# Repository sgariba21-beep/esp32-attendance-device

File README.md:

# ESP32 Fingerprint Attendance System

Ghanaian schools and institutions still take attendance on paper. A teacher calls a register, marks each name by hand, then copies the totals into another book or a spreadsheet. Roll-call takes class time and the handwritten tallies are easy to miscount and slow to total across a term. This system replaces the register with a fingerprint scan.

An ESP32 device with an R503 fingerprint sensor records each scan, and a Next.js dashboard backed by Supabase handles reporting and the day-to-day management of devices and members. One cloud Supabase project serves every institution, with each tenant's data isolated from the rest. It is in use at two schools and an office, with 13 devices and about 400 active members between them (see [Real-World Deployment](#real-world-deployment)).

---

## Why This Exists

- Ghanaian schools and small institutions track attendance on paper or not at all; the affordable end of the market has no biometric option tied to a reporting dashboard.
- ZKTeco and similar incumbents ship standalone terminals with no multi-tenant cloud dashboard and no remote device management.
- The system is built around term and academic-year structure, with institution type configurable as school, office, or shop.
- Each device is built from off-the-shelf parts at about GHS 1,000.
- The firmware and dashboard are AGPL-3.0 on GitHub; institutions can self-host or use the managed hosted service.

---

## Real-World Deployment

The system is in use at three sites: two schools and an office.

| Deployment | Sites | Devices | Active members |
|---|---|---|---|
| This repo (hosted service) | 1 school, 1 office | 2 | ~100 |
| OLAG (private repo) | 1 school | 11 | ~300 |
| **Total** | **3** | **13** | **~400** |

- **This repo.** One school and one office run on the hosted multi-tenant service, with one device each.
- **OLAG.** The second school has 11 devices: 10 for classes and 1 for its robotics club, which runs in club (meeting-based) mode. OLAG runs the same attendance system, with the same firmware, dashboard, and backend design. It lives in a separate repository with its own Supabase project and Vercel deployment because the school wanted private ownership of its source code.

---

## Architecture

```
┌─────────────────────────────┐
│       ESP32 Devices         │
│  R503 fingerprint sensor    │
│  One device per unit        │
└────────────┬────────────────┘
             │ HTTPS (x-device-secret / x-bootstrap-secret)
             ▼
┌─────────────────────────────┐
│  Supabase Edge Functions    │
│  (cloud)                    │
│  log-attendance             │
│  mark-absent (pg_cron)      │
│  get-enrollment-job         │
│  update-enrollment-job      │
│  register                   │
│  assignment-poll            │
└────────────┬────────────────┘
             │ service role
             ▼
┌─────────────────────────────┐
│   Supabase PostgreSQL       │
│   (cloud)                   │
│   Multi-tenant schema       │
│   RLS policies (defence-in- │
│   depth; dormant for svc    │
│   role access)              │
└─────────────────────────────┘
             ▲
             │ server-side only (service role)
┌────────────┴────────────────┐
│     Next.js Dashboard       │
│     Deployed on Vercel      │
│  All Supabase calls are     │
│  server-side (no browser    │
│  exposure of keys)          │
└─────────────────────────────┘
```

---

## Tech Stack

| Layer | Technology |
|---|---|
| Firmware | Arduino (ESP32), FreeRTOS, R503 fingerprint library, SH1106 OLED (Adafruit SH110X + GFX) |
| Database | Supabase (cloud PostgreSQL + Auth + Storage + pg_cron) |
| Edge functions | Deno (Supabase Edge Functions) |
| Dashboard | Next.js App Router, shadcn/ui, TailwindCSS |
| Dashboard PWA | Installable web app — `manifest.webmanifest` + a minimal service worker (installability only, no offline cache) and an in-app install prompt |
| Hosting | Vercel (dashboard) |

> **Note on Next.js:** This project uses a version with breaking API changes from standard Next.js. Middleware lives in `frontend/proxy.ts`, not `middleware.ts`. Read `frontend/AGENTS.md` before writing any Next.js code.

---

## Hardware

### Components

| Component | Spec |
|---|---|
| Microcontroller | ESP32 (dual-core, 240 MHz) |
| Fingerprint Sensor | R503 Capacitive |
| RTC Module | DS3231 |
| Display (optional) | SH1106 1.3" 128×64 I²C OLED @ address 0x3C (a 0.96" SSD1306 needs the pre-1.12.0 driver) — the firmware runs headless if it is absent or fails to init |
| Carrier PCB | Custom 2-layer KiCad interconnect board — no active parts; seats the ESP32 module and provides keyed connectors for the R503 (JST-SH), the RTC + OLED I²C group, and a JST-GH 5 V input. Source in [`hardware/PCBs/`](hardware/PCBs/) |
| Enclosure | 3D-printed base + lid (+ an OLED bezel variant for display builds). FreeCAD source and print-ready 3MF in [`hardware/CAD files/`](hardware/CAD%20files/) |
| Fasteners | M3 screws + M3 heat-set inserts — the brass inserts are melted into the printed enclosure with a soldering iron, and the screws thread into them |

### Wiring

| Signal | ESP32 Pin |
|---|---|
| R503 TX → ESP32 RX | GPIO 16 |
| R503 RX → ESP32 TX | GPIO 17 |
| DS3231 SDA | GPIO 21 |
| DS3231 SCL | GPIO 22 |
| OLED SDA | GPIO 21 (shared I²C bus with the DS3231) |
| OLED SCL | GPIO 22 (shared I²C bus with the DS3231) |

---

## Firmware Architecture

Single sketch: `firmware/ClassAttendance_Current_RTC/ClassAttendance_Current_RTC.ino`. Three FreeRTOS tasks pinned across the two cores.

### Tasks

| Task | Core | Responsibility |
|---|---|---|
| `FingerprintTask` | 1 | Scan loop, match against the local fid map, LED feedback, enrollment execution, captive-portal launch on master-finger scan. Writes each scan to SPIFFS then signals `NetworkTask` via binary semaphore. |
| `NetworkTask` | 0 | Provisioning, waiting on scan semaphore from `FingerprintTask`, rotate-then-process SPIFFS queue flush to `log-attendance`, NTP→RTC sync, WiFi reconnect, and a server-reachability watchdog that reboots the device after a sustained inability to reach the backend. |
| `EnrollmentTask` | 0 | Polls `get-enrollment-job`, hands jobs to `FingerprintTask`, reports results durably (retried until acknowledged), acts on the decommission signal (wipes identity and reboots into provisioning). |

Inter-task communication:

- `memQueueSem` is a binary semaphore used only as a signal: `FingerprintTask` gives it after writing a scan to SPIFFS; `NetworkTask` waits on it (or a 15 s periodic timeout) before calling `flushQueue()`. There is no in-memory scan queue.
- Enrollment jobs pass from `EnrollmentTask` to `FingerprintTask` through `currentEnrollJob`, guarded by `enrollMutex` and signalled by `enrollSem`.
- `spiffsMutex` serialises every SPIFFS access across all three tasks.

### Display (OLED)

An optional 1.3" SH1106 128×64 panel on the shared I²C bus. `display.begin()` is attempted once in `setup()`; on failure `displayAvailable = false` and the firmware runs headless with no behaviour change. There is no dedicated display task — rendering is driven from a Core-0-safe mailbox. Tasks post card state (idle clock, scan verdict, enrollment step, master-finger confirm, provisioning, OTA) into the mailbox and never touch the `display` object directly. Tier-2 status (queue depth, dropped-record count, degraded / offline) is overlaid on the idle screen; the panel sleeps after 120 s idle and wakes on the next event. The per-institution `member_name_display` setting (fetched via `get-enrollment-job`, cached in SPIFFS with `config_rev`) controls how much of a member's name a scan card shows.

### Offline queue

- **Durability-first:** each scan is written to `/queue.txt` in SPIFFS synchronously inside `FingerprintTask` before any network attempt. The scan is never held only in RAM.
- **Rotate-then-process:** when `NetworkTask` flushes, it atomically renames `/queue.txt` → `/queue_inflight.txt` under the lock, then releases the lock. `FingerprintTask` can keep appending to a fresh `/queue.txt` while the network send runs without holding `spiffsMutex`.
- **Crash recovery:** if power is cut mid-flush, `/queue_inflight.txt` is orphaned. On the next boot, `recoverInflightQueue()` runs before tasks start and merges it back into `/queue.txt`.
- On flush, 5xx/429/network errors keep a record for retry; 4xx drops it.
- Caps: 1000 entries, 256 KB, 7-day age. Oldest records are trimmed first.

### Scan IDs

Each scan gets a `scan_id` of `scan-YYYYMMDDhhmmss-<member-sid>`, with the timestamp read from the DS3231 RTC. The RTC clock survives reboots and power loss and is synced from NTP on boot and after each reconnect.

### OTA

- On boot, with WiFi up and assignment not pending, the device waits a random jitter of 0–120 s (seeded from hardware entropy) before checking for updates. This prevents a fleet-wide power blip from hitting GitHub's 60 req/hr unauthenticated rate limit simultaneously.
- The device GETs `releases/latest` from the GitHub API. Release tags must be `firmware-v<major>.<minor>.<patch>`. The tag version is compared against the compiled-in `FIRMWARE_VERSION`; only a strictly newer version flashes.
- The release's `.bin` asset is streamed through the `Update` library. The sensor LED holds red while writing, and the device reboots into the new image on success.

---

## Database Schema

All dashboard data access uses `createAdminClient()` (service role — bypasses RLS). RLS policies exist as defence-in-depth and will become load-bearing if authenticated client access is introduced.

```sql
-- Institution registry (one row per tenant)
-- type: 'school' | 'office' | 'shop'
-- theme_primary: hex brand colour injected as CSS custom properties server-side (no FOUC)
-- theme_preset: curated palette key (e.g. 'indigo', 'rose') or 'custom'; null → platform default
-- device_secret: shared bootstrap secret — TRANSITIONAL. Will be removed once all
--   devices have been re-provisioned with per-device secrets (devices.device_secret).
-- tracked_weekdays: smallint[] of ISO weekday numbers (1=Mon … 7=Sun) attendance is
--   tracked on. Replaces the removed skip_weekends boolean. log-attendance ignores
--   scans on other days; mark-absent generates no rows for them.
-- time_format: '12h' | '24h' — dashboard clock rendering only; stored times stay UTC / 24h.
-- track_lateness / expected_start_time / late_grace_minutes and
--   track_early_leaving / expected_end_time / early_leave_grace_minutes:
--   optional per-institution punctuality thresholds that drive attendance.punctuality.
-- member_name_display: 'full' | 'first' | 'initial_last' | 'sid' | 'none' — how much of a
--   member's name the device OLED shows on a scan card (enrollment always shows the full name).
-- currency: ISO-4217 display currency for the retail module (formatting only, no FX).
-- sell_products / sell_services / loyalty_enabled: shop-module switches.
-- status: 'active' | 'suspended' | 'deactivated' — non-active tenants are gated to /suspended.
-- config_rev: bigint bumped by the institutions_touch trigger on any row change; the device
--   polls it to know its cached device_config is stale. updated_at is bumped by the same trigger.
institutions    (id, name, type, logo_url, label_member, label_members, label_group,
                 label_unit, label_period, label_staff, label_staff_plural,
                 track_students, track_staff, student_scan_mode, staff_scan_mode,
                 tracked_weekdays, timezone, time_format, track_lateness,
                 expected_start_time, late_grace_minutes, track_early_leaving,
                 expected_end_time, early_leave_grace_minutes, member_name_display,
                 currency, sell_products, sell_services, loyalty_enabled, status,
                 device_secret, config_rev, created_at, updated_at,
                 theme_primary, theme_preset)

-- Members (students, staff, customers, etc.) — scoped to institution
-- member_type: 'student' | 'staff'  (default 'student')
-- sid is UNIQUE PER INSTITUTION (institution_id, sid), not globally
-- device_id FK is ON DELETE SET NULL (device deletion preserves member records)
members         (id, sid, fullname, group_name, unit_name, fin1, fin2, status, member_type,
                 device_id→devices SET NULL, institution_id, created_at)

-- One ESP32 per unit — scoped to institution
-- device_secret: per-device secret issued at provisioning time by /assignment-poll
-- revoked: true blocks the device from logging attendance (instant lockout)
-- provisioning_token: issued by /register, required by /assignment-poll (H7)
devices         (id, group_name, unit_name, display_name, mac, provisioning_token,
                 device_secret, revoked, institution_id)

-- Academic periods — scoped to institution (nullable for office/shop-type institutions)
periods         (id, term, year, status, start_date, end_date, institution_id)

-- Attendance records — scoped to institution
-- status: 'present' | 'absent'
-- scan_type: 'present' | 'time_in' | 'time_out'  (CHECK constraint — 'absent' is a status, not a scan_type)
-- punctuality: 'on_time' | 'late' | 'early_leave' | null — verdict fixed at scan time from the
--   institution's thresholds; null when tracking is off or the row is a mark-absent placeholder
-- date/time are stored in the INSTITUTION's timezone (log-attendance + mark-absent agree)
-- scan_id is UNIQUE PER INSTITUTION (institution_id, scan_id); dedup also on (member_id, date, scan_type)
-- device_id FK is ON DELETE SET NULL
attendance      (id, member_id→members, period_id→periods, device_id→devices SET NULL,
                 date, time, status, scan_type, punctuality, scan_id, institution_id)

-- Remote fingerprint enrollment queue
-- command: 'register' | 'delete' | 'clearall' | 'register-master' | 'delete-master'
-- member_id: FK→members (renamed from student_id). NULL for clearall / register-master / delete-master.
-- allow_overwrite: operator confirmed overwriting an already-occupied sensor slot
--   (register / register-master only). The device refuses an occupied slot unless this is true.
-- dispatched_at / attempts / last_error: dispatch tracking. get-enrollment-job re-delivers a job
--   stuck in_progress past a timeout and auto-fails it (with last_error) after a capped number of
--   attempts. The enrollment_jobs_status_guard trigger makes 'completed' / 'failed' terminal.
-- device_id FK is ON DELETE SET NULL
enrollment_jobs (id, device_id→devices SET NULL, member_id→members, finger_slot,
                 command, status, fid, note, allow_overwrite, dispatched_at, attempts,
                 last_error, institution_id, created_at)

-- Holidays (date ranges) — scoped to institution
-- recurring: true = matched by month/day every year (year-wrap ranges supported)
holidays        (id, label, start_date, end_date, recurring, institution_id)

-- Dashboard user roles — scoped to institution (platform_admin has null institution_id)
-- assigned_device_id: FK that pins a session to one device. REQUIRED for teacher/staff
--   (unresolved → they see nothing); OPTIONAL for admin (bound → records + enrollment
--   scoped to that device; unbound → whole institution). Preferred over the legacy
--   assigned_unit string; backfilled by migration. Resolved by dal.ts resolveDeviceScope().
profiles        (id→auth.users, role, assigned_unit, assigned_device_id→devices SET NULL,
                 institution_id)

-- Deferred SPIFFS-wipe queue — no FK, survives device row deletion
device_resets   (device_id UUID, created_at)

-- Polling watermark — one row per institution, updated by triggers on attendance,
-- members, devices, and periods. The dashboard polls /api/changes every 12 s and
-- calls router.refresh() only when last_change_at has advanced. Replaces the
-- previous SSE-based realtime stream (eliminated REPLICA IDENTITY FULL WAL amplification).
institution_activity  (institution_id PK→institutions, last_change_at timestamptz)
```

### Migrations

All migrations are in `backend/supabase/migrations/`. They must be reviewed and applied manually — do not auto-apply to cloud.

---

## Auth & RBAC

Authentication uses Supabase Auth (server-side only — all Supabase calls go through Next.js server components and API routes, never from the browser).

### Account Types

| Role | Scope | Access |
|---|---|---|
| `platform_admin` | Cross-institution (no institution_id) | All pages, bypasses all role gates, operates via service role. Responsible for creating institutions and bootstrapping first super_admin per institution. |
| `super_admin` | Institution-scoped | All pages — devices, enrollment, promotion, academic, members, attendance, user management. Can manage users within their institution but cannot create platform_admins. |
| `admin` | Institution-scoped (optionally device-scoped) | Members, academic, promotion, attendance — no devices or enrollment. May optionally be pinned to a single device via `assigned_device_id`; when pinned, attendance/members and enrollment are scoped to that device, otherwise the whole institution. |
| `teacher` | Institution-scoped, unit-scoped | Read-only attendance and members, filtered to their `assigned_device_id` (FK, with `assigned_unit` string-match fallback for unbackfilled profiles). |
| `staff` | Institution-scoped, unit-scoped | Same as teacher — read-only attendance and members, filtered to their unit. The `/staff` roster page is not visible in the nav for this role. |
| `cashier` | Institution-scoped (shop type) | Sales, Clients, and Catalog pages only. Intended for retail staff at shop-type institutions. Cannot access attendance, members, devices, or admin pages. |

### How it works

- `frontend/lib/supabase/dal.ts` exports `verifySession()`, `requireRole(...roles)`, `getInstitution(institutionId)`, `resolveInstitutionScope(session, institutionParam?)`, and `resolveDeviceScope(session)` (returns `{ mode: 'all' | 'device' | 'none' }` — the single device a session is pinned to, if any).
- `verifySession()` and `getInstitution()` are both `cache()`-wrapped — one DB hit per render cycle regardless of how many components call them.
- `requireRole()` calls `verifySession()` and redirects to `/unauthorized` if the role doesn't match. `platform_admin` bypasses all role checks.
- `resolveInstitutionScope()` enforces tenant scoping: platform_admin may pass an explicit institution param; all other roles are always locked to their own `institution_id` regardless of query params.
- **Fail-closed:** an authenticated user with no `profiles` row (or no role) is redirected to `/unauthorized` — it does **not** default to any role. Public sign-up is disabled in Supabase Auth; accounts are created only via `/users` and `/onboarding`.
- **Tenant ownership:** because the dashboard uses the service role (RLS bypassed), every mutating server action verifies the target record belongs to the caller's institution via `lib/supabase/ownership.ts` (`ownsRecord`). `platform_admin` is cross-tenant by design.
- The dashboard layout calls `verifySession()` and passes `role` to the sidebar and mobile nav, which filter nav items by role.
- `teacher` and `staff` are always device-scoped via `assigned_device_id` (FK, preferred) or `assigned_unit` (legacy string); an unresolved assignment means they see nothing, never everything. `admin` may optionally carry the same binding. Attendance and member data — and the CSV export (`/api/attendance/export`) — is filtered server-side to that device before rendering.
- Run `node scripts/check-rbac.mjs` (from `frontend/`) to verify every page under `(dashboard)` has a `requireRole(` call. Exits 1 with a list if any are ungated.

### Creating the first super_admin (per institution)

After creating an institution in Supabase, insert a profile row for the Supabase Auth user:

```sql
insert into profiles (id, role, institution_id)
values ('<auth-user-uuid>', 'super_admin', '<institution-uuid>');
```

Additional accounts are managed through the `/users` page in the dashboard.

---

## Dashboard Pages

### Attendance & roster (all institution types)

| Route | Access | Description |
|---|---|---|
| `/` | All roles | Overview — today's present/absent counts, attendance rate, and a recent-activity feed (last 8 scans). `teacher`/`staff` see only their unit. `platform_admin` sees a cross-tenant summary: institution count, active members, devices online, and total scans today. |
| `/attendance` | All roles | Attendance records with date, period, member, unit, status, and type filters. Per-member stats panel. Results paginated at 50 rows. `teacher`/`staff` see only their unit; a teacher with no device assigned sees an empty-state prompt to contact their administrator. Time-in/time-out pairs shown on a single row, with **Late** / **Early** badges when the institution has punctuality thresholds enabled. CSV export available. |
| `/members` | All roles except cashier | Member roster (non-staff). `teacher`/`staff` see only their unit, no edit controls. |
| `/staff` | super_admin, admin, platform_admin | Staff member roster. Visible only when `track_staff = true`. |
| `/devices` | super_admin, platform_admin | ESP32 device registry and provisioning — assign unregistered devices to units, revoke devices. Search + institution filter for platform_admin. Devices only enter via physical provisioning (no manual create). |
| `/academic` | super_admin, admin, platform_admin | Academic periods and holidays. Nav label is "Academic" (school), "Periods & Holidays" (office), or "Closed Days" (shop — holidays only). Supports recurring (yearly) holidays matched by month/day. |
| `/enrollment` | super_admin, platform_admin | Fingerprint enrollment job queue — `register`, `delete`, `clearall`, `register-master`, `delete-master` commands sent to devices, with retry / cancel controls for failed or stuck jobs (jobs stranded `in_progress` are also re-delivered and self-healed server-side). Validates member institution + device assignment before dispatching. Institution column for platform_admin. |
| `/promotion` | super_admin, admin, platform_admin | Bulk year-end promotion — moves members to the next group, resets finger slots, deactivates final-year members. School-type institutions only. |
| `/settings` | super_admin, platform_admin | Institution config — name, logo, brand colour, type, label overrides, per-type scan modes, tracked weekdays (7-day selector, replaces skip_weekends), late-arrival / early-departure thresholds, timezone, 12h/24h time display, name-shown-on-device, and (shop) currency / offerings / loyalty toggles. |
| `/institutions` | platform_admin | All institutions with member/device counts. Edit or delete any institution (deletion fans out SPIFFS wipe to all assigned devices). |
| `/institutions/[id]` | platform_admin | Edit a specific institution's settings. |
| `/onboarding` | platform_admin | Create a new institution and its first super_admin account. Includes timezone selector (Africa/Accra default) and neutral label presets for shop-type institutions. |
| `/users` | super_admin, admin, platform_admin | Dashboard account management. `admin` can view the list and change their own password only. `super_admin`/`platform_admin` can create, edit, and delete accounts. |
| `/unauthorized` | — | Shown when a user navigates to a page their role cannot access. |
| `/suspended` | — | Shown when a user's institution is suspended/deactivated. Lives outside `(dashboard)` to avoid re-entering `verifySession`. Sign-out is the only available action. |

### Retail / loyalty (shop-type institutions only)

| Route | Access | Description |
|---|---|---|
| `/sales` | super_admin, admin, cashier | Record sales transactions. Line-item entry with catalog lookup, optional staff assignment, per-sale note. Low-stock warning surfaced as a non-blocking alert after a successful sale. |
| `/clients` | super_admin, admin, cashier | Client roster with visit history and loyalty point balance. Search by name or phone. |
| `/catalog` | super_admin, admin, cashier | Products and services catalog. Stock quantity tracked for products; low-stock threshold warnings on the Reports page. |
| `/rewards` | super_admin, admin | Loyalty reward redemption and tier management. Gated additionally by `loyalty_enabled` on the institution. |
| `/reports` | super_admin, admin | Sales analytics — daily/weekly takings, revenue by client and staff member, popular items, visit frequency, low-stock products, loyalty rewards issued. CSV export for takings, client revenue, and staff revenue. |

### Screenshots

Dark-mode captures of the dashboard live in [`images/`](images/) — one set per
institution type (50 pages in all). See [`images/README.md`](images/README.md)
for the full index.

> **Disclaimer — dummy data.** Every screenshot is taken from throwaway demo
> institutions (Riverdale High School, Northwind Logistics, Curbside Cycle Co.,
> Lakeside Chess Club) created solely for documentation. All names, clients,
> sales, attendance records and figures shown are fabricated — not real people,
> and not the real institutions that use this system.

---

## Device Authentication & Provisioning

### Provisioning (new devices)

1. Device boots with no `device_identity.json` in SPIFFS.
2. Calls `POST /register` with its MAC address (`x-bootstrap-secret` header).
3. Receives a `device_id`, a `provisioning_token`, and `status: "pending"`. The device persists both to `provisioning.json` so a reboot keeps the token.
4. Shows yellow breathing LED and polls `POST /assignment-poll` every 5 s, sending `{ device_id, provisioning_token }`.
5. An admin assigns the device from the dashboard `/devices` page.
6. Poll returns `status: "assigned"` with `institution_id`, `device_secret` (per-device), `display_name` — **only if the provisioning_token matches** (otherwise 401).
7. Device writes `device_identity.json` to SPIFFS, deletes `provisioning.json`, and begins normal operation.

> **TLS:** the firmware validates server certificates (`certs.h` → `ROOT_CA_BUNDLE`, includes intermediates for WE1/Sectigo DV E36 — mbedTLS cannot do AIA fetching).
> The bootstrap secret lives in `secrets.h` (gitignored). Copy `secrets.example.h` → `secrets.h` and set the same value as the `BOOTSTRAP_SECRET` secret in Supabase Edge Functions.

### Normal operation

- Every scan: `POST /log-attendance` with `{ device_id, ... }` body and `x-device-secret: <per-device secret>` header. A transitional dual-path also accepts the legacy shared `institutions.device_secret` for devices not yet re-provisioned.
- Enrollment polling: `POST /get-enrollment-job` with `{ device_id }`, authenticated via per-device secret. A job left `in_progress` past a timeout (device rebooted, ack lost) is re-delivered, and auto-failed after a capped number of attempts.
- Enrollment result: `POST /update-enrollment-job` with `{ id, device_id, institution_id, status, ... }`, authenticated via per-device secret. `institution_id` is derived server-side from the device row — the body value is ignored. The device retries this report until it lands (firmware ≥ 1.10.0); the `enrollment_jobs_status_guard` trigger keeps a terminal `completed` / `failed` status from being pulled backwards by a late write.
- Decommission signal: if `get-enrollment-job` returns `decommissioned: true`, the device wipes its identity and reboots. The `device_resets` row persists until the device re-registers (not consumed on read — durable against race conditions).
- `pg_cron` calls `POST /mark-absent` daily with `x-cron-secret`. Processes institutions in batches of 8 concurrently. **Requires the `pg_net` extension** — enable it in the Supabase dashboard under Database → Extensions.

### Revoking a device

Set `devices.revoked = true` in the database. The device's next `log-attendance` call receives 401 immediately. For permanent decommission, also insert into `device_resets`.

### OTA

Firmware checks `https://api.github.com/repos/sgariba21-beep/esp32-attendance-device/releases/latest` on boot after a random jitter delay. Releases must be tagged `firmware-v<version>` (e.g. `firmware-v1.10.0`; current `FIRMWARE_VERSION` is `1.10.0`). The `.bin` asset is downloaded and flashed via the ESP32 `Update` library.

---

## Key Files

```
esp32-attendance-device/
├── README.md
├── docs/
│   ├── README.md                           ← index: which document is for whom, what to hand over
│   ├── for-clients/                        ← PDFs for institutions: role guides, type guides, privacy note
│   ├── for-operators/                      ← platform manual, technical docs, secret-rollout guide, e2e checklist
│   └── source/                             ← Markdown sources + build.py — edit these, not the PDFs
├── firmware/
│   └── ClassAttendance_Current_RTC/
│       ├── ClassAttendance_Current_RTC.ino ← ESP32 firmware (single sketch)
│       ├── certs.h                         ← ROOT_CA_BUNDLE (includes intermediates)
│       ├── secrets.example.h               ← template for secrets.h (gitignored)
│       └── secrets.h                       ← BOOTSTRAP_SECRET — gitignored, create from example
├── backend/
│   └── supabase/
│       ├── config.toml                     ← edge function config (verify_jwt = false for all)
│       ├── migrations/                     ← applied to cloud manually; do NOT auto-apply
│       └── functions/
│           ├── log-attendance/             ← dual-path auth: per-device + transitional shared secret
│           ├── mark-absent/                ← BATCH_SIZE=8 concurrent; recurring holiday support
│           ├── get-enrollment-job/         ← per-device auth; decommission signal is persistent
│           ├── update-enrollment-job/      ← per-device auth; institution derived from device row
│           ├── register/
│           └── assignment-poll/            ← issues per-device secret on first assignment
└── frontend/
    ├── proxy.ts                            ← Next.js middleware (NOT middleware.ts); matcher excludes
    │                                         /api, _next, and the PWA assets (manifest.webmanifest, sw.js, icons/)
    ├── next.config.ts                      ← sends Cache-Control: no-cache for /sw.js
    ├── AGENTS.md                           ← read before writing any Next.js code
    ├── scripts/
    │   ├── check-rbac.mjs                 ← CI guard: exits 1 if any dashboard page lacks requireRole
    │   └── generate-icons.mjs             ← regenerates the PWA icon set from the SVG source
    ├── app/
    │   ├── manifest.ts                    ← web app manifest, served at /manifest.webmanifest (platform branding only)
    │   ├── (auth)/login/                  ← password is NOT trimmed before submission
    │   ├── (dashboard)/
    │   │   ├── layout.tsx                 ← verifySession, generateMetadata (dynamic tab title)
    │   │   ├── (admin)/layout.tsx         ← route-group gate for admin-only pages
    │   │   ├── attendance/
    │   │   ├── members/
    │   │   ├── staff/
    │   │   ├── devices/
    │   │   ├── academic/
    │   │   ├── enrollment/
    │   │   ├── promotion/
    │   │   ├── settings/
    │   │   ├── institutions/[id]/
    │   │   ├── onboarding/
    │   │   ├── users/
    │   │   ├── sales/                     ← shop only; low-stock warning after sale
    │   │   ├── clients/                   ← shop only; visit history + loyalty balance
    │   │   ├── catalog/                   ← shop only; products + services
    │   │   ├── rewards/                   ← shop only; loyalty_enabled gate
    │   │   └── reports/                   ← shop only; takings, revenue, low-stock analytics
    │   ├── api/
    │   │   ├── signin/
    │   │   ├── signout/
    │   │   ├── enrollment-stream/         ← SSE stream for enrollment job updates (kept)
    │   │   ├── realtime-stream/           ← 410 tombstone — use /api/changes instead
    │   │   ├── changes/                   ← watermark poll endpoint (replaces SSE stream)
    │   │   ├── attendance/export/         ← CSV export with full filter parity
    │   │   └── reports/{takings,clients,staff}/export/  ← shop report CSV exports
    │   ├── suspended/                     ← institution suspended; sign-out only
    │   └── unauthorized/
    ├── lib/
    │   ├── types.ts                       ← shared TS types
    │   ├── theme.ts                       ← per-institution brand theming
    │   └── supabase/
    │       ├── dal.ts                     ← verifySession, requireRole, getInstitution,
    │       │                                 resolveInstitutionScope, resolveDeviceScope, UserRole
    │       └── server.ts                  ← createAuthClient, createAdminClient
    └── components/
        ├── sidebar.tsx
        ├── mobile-header.tsx
        ├── mobile-bottom-nav.tsx
        ├── theme-toggle.tsx
        ├── realtime-refresh.tsx           ← polls /api/changes every 12 s; router.refresh() on watermark advance
        ├── session-manager.tsx            ← inactivity timeout + sessionStorage guard
        ├── pwa/                           ← service-worker registration + in-app install prompt
        └── ui/
            └── single-select.tsx
```

---

## Phase Status

| Phase | Description | Status |
|---|---|---|
| 1 | Cloud deployment (single-tenant) | ✅ Complete |
| 2 | Multi-tenant schema + edge functions | ✅ Complete |
| 3 | Firmware provisioning flow | ✅ Complete |
| 4 | Frontend — de-brand, institution config, devices page, settings | ✅ Complete |
| 5 | Captive portal — WiFi-only | ✅ Complete |
| 6 | Retail / loyalty module — shop-type tenants, cashier role, sales/clients/catalog/rewards/reports | ✅ Complete |
| 7 | Security hardening — per-device secrets, SPIFFS-only durable queue, tenant isolation fixes, polling watermark | ✅ Complete |
| 8 | OLED display — device-side status screen: idle clock, scan / enrollment / portal / master-confirm cards, degraded & offline states | ✅ Complete |
| 9 | Reliability & reach — enrollment-job self-healing (re-delivery, retry/cancel, status guard), firmware server-reachability watchdog, per-institution tracked weekdays / time format / punctuality thresholds, installable PWA | ✅ Complete |

---

## Contributing

See [CONTRIBUTING.md](CONTRIBUTING.md) for the repo layout and local setup steps for the frontend and firmware.

---

## License

AGPL-3.0. See [LICENSE](LICENSE).

Network use of a modified version requires releasing source under the same license. Contact sgariba21@gmail.com for commercial licensing or self-hosting arrangements.

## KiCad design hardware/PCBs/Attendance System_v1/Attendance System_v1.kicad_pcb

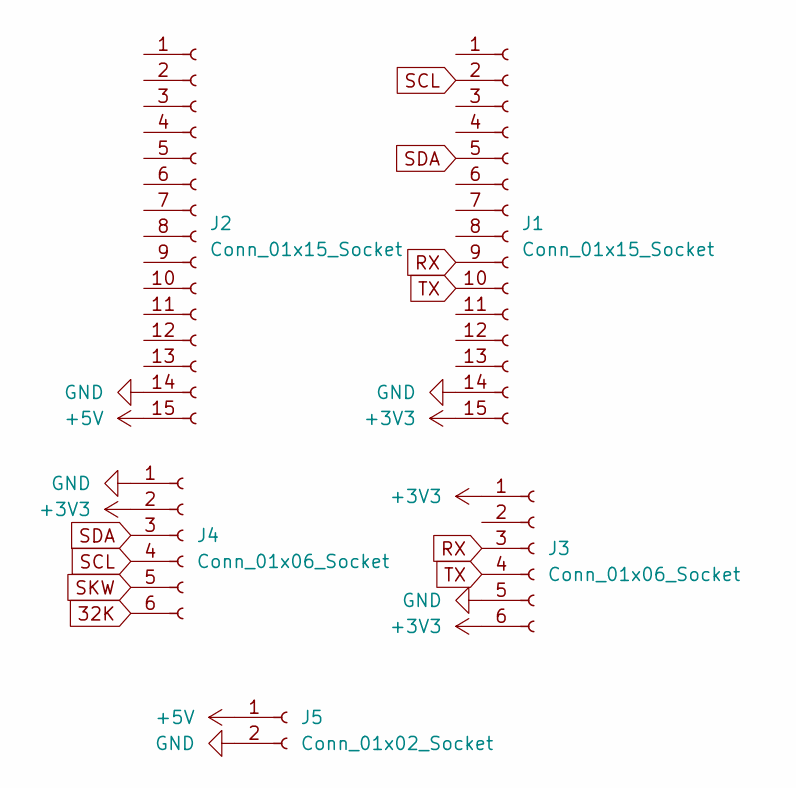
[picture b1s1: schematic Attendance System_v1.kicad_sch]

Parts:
J1, J2: Conn_01x15_Socket; PinSocket_1x15_P2.54mm_Vertical
J3: Conn_01x06_Socket; JST_SH_BM06B-SRSS-TB_1x06-1MP_P1.00mm_Vertical
J4: Conn_01x06_Socket; PinSocket_1x06_P2.54mm_Vertical
J5: Conn_01x02_Socket; JST_GH_BM02B-GHS-TBT_1x02-1MP_P1.25mm_Vertical

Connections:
32K: J4.6
+3V3: J1.15, J3.1, J3.6, J4.2
+5V: J2.15, J5.1
GND: J1.14, J2.14, J3.5, J4.1, J5.2
RX: J1.9, J3.3
SCL: J1.2, J4.4
SDA: J1.5, J4.3
SKW: J4.5
TX: J1.10, J3.4

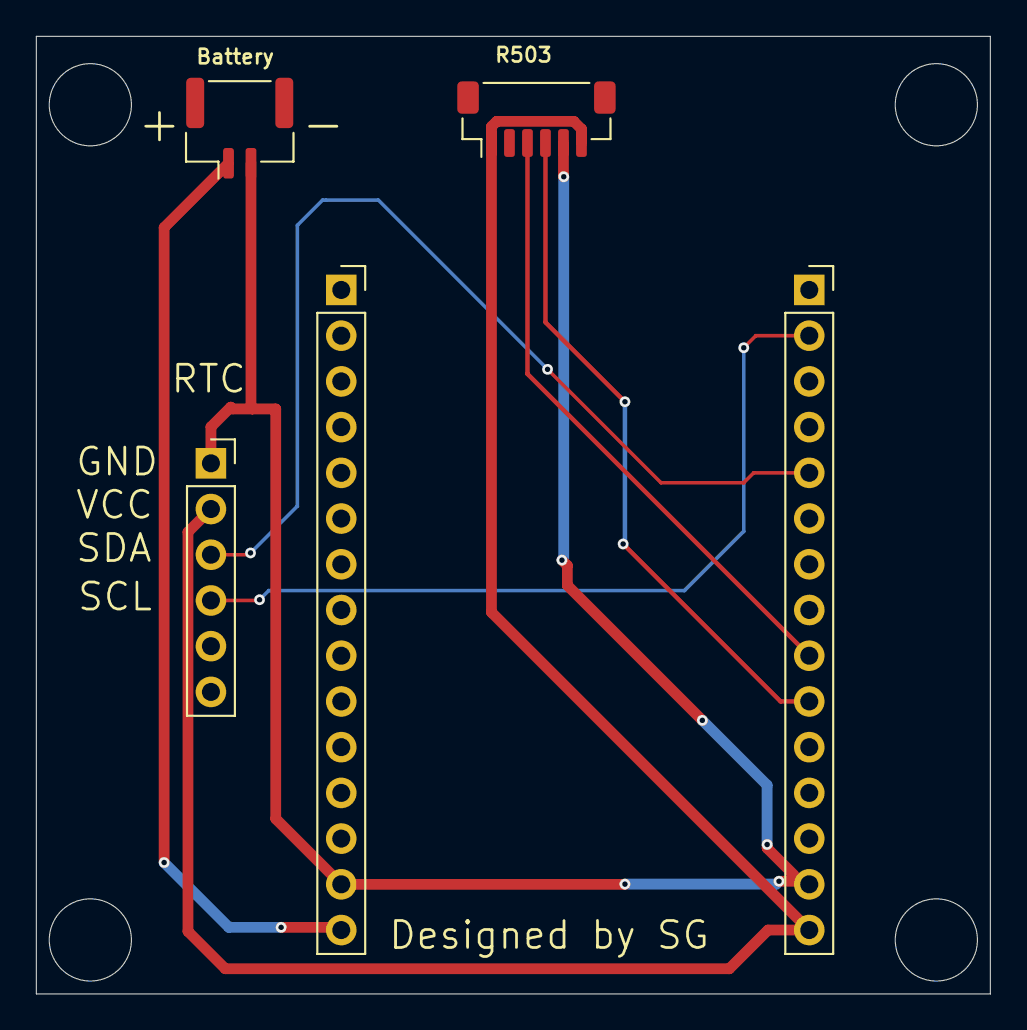
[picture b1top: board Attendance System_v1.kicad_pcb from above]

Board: 2 copper layers, 53.0 x 53.2 mm, 5 parts (0 on the bottom side), 7 nets.

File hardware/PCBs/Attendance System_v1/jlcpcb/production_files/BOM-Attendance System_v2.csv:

Comment,Designator,Footprint,LCSC,Quantity
Conn_01x06_Socket,J3,JST_SH_BM06B-SRSS-TB_1x06-1MP_P1.00mm_Vertical,,1
Conn_01x15_Socket,J2,PinSocket_1x15_P2.54mm_Vertical,,1
Conn_01x15_Socket,J1,PinSocket_1x15_P2.54mm_Vertical,,1
Conn_01x02_Socket,J5,JST_GH_BM02B-GHS-TBT_1x02-1MP_P1.25mm_Vertical,,1
Conn_01x06_Socket,J4,PinSocket_1x06_P2.54mm_Vertical,,1

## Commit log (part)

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2026-03-25 Update README.md
    Removed the MIT license badge from the README.
2026-03-25 Create temp
2026-03-28 Move ClassAttendance_Current_RTC.ino into subdir
    Rename firmware/ClassAttendance_Current_RTC.ino to firmware/ClassAttendance_Current_RTC/ClassAttendance_Current_RTC.ino to organize firmware files into a dedicated directory. No code changes were mad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
2026-04-01 Revert "Update ClassAttendance_Current_RTC.ino"
    This reverts commit 72d3cfd028bf54c16a1765b352a23133351c1976.
2026-04-01 Add WiFi captive portal and network refactor
    Introduce a captive portal to provision WiFi credentials and persist them to SPIFFS; device will restart after saving. Added load/save helpers (WIFI_CREDS_FILE), a WebServer + DNSServer portal with a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
    Other notable changes: adjust HTTP timeouts/retry/backoff and improve error handling for POST/GET requests; remove local master enrollment mode an
2026-04-03 Remove teacher FID fallbacks and simplify mapping
    Remove hardcoded teacher/student fingerprint ID ranges and the TEACHERS_IDS_FALLBACK array so the device no longer seeds fid_map from built-in fallbacks. loadFidMapFromFS() now starts with an empty m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
2026-04-06 Enclosure Fixes
2026-04-06 Enclosure stuff
2026-04-06 OTA update test
2026-04-06 Revert "Changed binaries"
    This reverts commit e39a3bfe60a7b5cce8a2b31cef5ac6af26820c98.
2026-04-06 Revert "OTA update test"
    This reverts commit 4b48d43435ffae8945baa305c59cd97876fde186.
2026-04-08 Enclosure Monitoring
2026-04-10 Update Class_Attendance_Apps_Script.js
    Changed backend to suit office attendance
2026-04-11 Added SPIFFS queue trimming
    Set hard cap on SPIFFS queue, and discards entries older than 7 days
2026-04-11 Fully replaced "teacher" and "student" with "employee"
2026-04-11 Update Class_Attendance_Apps_Script.js
    Added monthly archiving to google sheet. Added deletion of already archived entries from the main attendance sheet
2026-04-11 Added captive portal fallback
    Enter captive portal if unrecognized finger is scanned 10 times in 30 seconds
2026-04-11 Added mounting extensions to enclosure
2026-04-15 Added proper dimensions to mounting screw holes
2026-04-17 Properly enforce SPIFFS queue trimming
2026-04-17 Updated README, and added setup guide
2026-04-17 Added employee "position" to all payloads, and created sheet setup function
2026-04-17 Updated comments, README, and pre-handover guide to reflect new changes
2026-04-18 Finishing touches on handover guide and admin manual
2026-04-18 Reverted Portal Fallback Commit
2026-04-19 Added admin manual, pre-handover guide, and updated README
2026-04-26 add OTA firmware update support with variant-based release management
    - Add checkAndApplyOTA() called at boot after sensor and tasks are initialized
    - Fetch latest release from GitHub Releases API and compare against FIRMWARE_VERSION
    - Parse browser_download_url from API response to locate .bin asset
    - Resolve GitHub CDN redirect manually before binary download to avoid begin() failure
    - Split API call, redirect resolution, and binary download into separate scopes to
    prevent heap exhaustion from concurrent WiFiClientSecure instances (~21KB headroom
2026-04-27 Improved dedupe logic
2026-04-27 Added spreadsheet initialization function
2026-04-27 Added termly sheet archiving by admin menu
2026-05-01 Remove portal fallback
2026-05-01 Recalculate attendance % for all students each time a scan is received
2026-05-08 Added scan logging
2026-05-08 Improved deduplication
2026-05-16 Fixed branch id not being stored properly
2026-06-02 Supabase Initial Config
2026-06-02 Enable Row Level Security (RLS)
2026-06-02 Created log-attendance function
2026-06-02 Create 20260602080000_add_device_id_to_students.sql
    Changed class column in students to device_id which references id from devices to find the student's class
2026-06-02 Changed class in students to device_id
    device_id in students table references id from devices table in order to get students' classes
2026-06-02 Remove dname from devices
2026-06-05 Added enrollment jobs table
2026-06-06 Started frontend dashboard
    Scaffolded NextJS project and added user authentication through created Supabase accounts
2026-06-06 Added student management page
2026-06-06 Added filtering to students page
2026-06-06 Added academic (term/year) management page
2026-06-06 Added enrollment page
2026-06-06 Added enrollment page and interfaced it with esp32
2026-06-06 Added student promotion page
2026-06-07 Added deletion of master fingerprints
2026-06-07 Added realtime updating
2026-06-07 Full (almost) UI redesign
2026-06-07 Stopped marking present on weekdays, holidays, and vacations
2026-06-07 Added auto-signout after 10 minutes and when the page is closed
2026-06-08 Fixed error when opening Devices page
2026-06-08 Made all tables scrollable on mobile
2026-06-08 Update attendance-view.tsx
    -The students filter should only show students from the selected class(es) and not all students at a time
2026-06-08 Changed "completed" badge from blue to green
2026-06-08 Changed dates into human-readable format
2026-06-08 Green badges for all positive statuses
2026-06-08 Changed term dates to human-readable format
2026-06-09 Fixed mark-absent not running at scheduled time
2026-06-12 Fixed mark-absent function not running by adding a new secret key
2026-06-12 Added 5-minute lockout after 3 failed login attempts
2026-06-12 Added pagination to attendance page
2026-06-12 Enrollment student dialog now loads only students from the selected class
2026-06-12 Replaced every "..." with a loader icon
2026-06-12 Upgraded the look of empty states
2026-06-12 Added white accent to active links on the sidebar
2026-06-12 Login page polish
    -Added subtle shadow to login dialog box
    -Disabled input and increased opacity when signing in
2026-06-12 Grouped attendance bar filters
2026-06-12 Moved fingerprint slots from directly being shown in the students page to showing in the "edit student" dialog
2026-06-12 Removed opacity of "Activate" button in inactive student rows
2026-06-12 Grouped devices by form on the devices page
2026-06-12 Past holidays now display as muted text
2026-06-12 Color coded entries in the command column of the enrollement page
2026-06-12 More UI improvements
2026-06-13 Fixed mobile functionality
    -Fixed navbar not showing up properly on mobile
    -Fixed mobile login problem
2026-06-13 Created profiles table
    -Columns: id, role, assigned_class
    -Roles: super_admin, admin, teacher
2026-06-13 Created /unauthorized page
2026-06-13 Gated pages per account type
2026-06-13 Added /users page for super_admins to manage users
2026-06-13 Teachers can only see stuff related to their class
2026-06-13 There must always be at least one super admin
2026-06-13 Updated README to reflect current project structure
2026-06-13 Deployed database to Supabase cloud
2026-06-13 Phase 2 (Creation of new tables and edge functions) complete
2026-06-13 Updated firmware entirely to match new multi-tenant system
2026-06-14 Add platform_admin bypass to requireRole and nav items
2026-06-14 Implement Phase 4: multi-tenant architecture, dynamic labels, and scan modes
    - Add institution_id to verifySession(); scope all dashboard queries per tenant
    - Load InstitutionConfig in layout; pass to sidebar, mobile nav, and page labels
    - Replace hardcoded OLAG branding and Student/Class/Term strings with dynamic
    institution labels (label_member/members/group/unit/period)
    - Rename /students → /members throughout (route, actions, revalidatePath, nav)
    - Devices: show unassigned (pending) devices for platform_admin; add AssignDevice
2026-06-14 Added tracking for both students and staff in the same institution
2026-06-14 Fixed build error
2026-06-14 Fixed UI display stuff
2026-06-14 No academic tab for office institutions
2026-06-14 More UI and terminology fixes
2026-06-14 feat: two-phase device assignment — platform admin binds institution, institution admin configures group/unit
    Removes group/unit fields from AssignDeviceDialog (platform admin now only picks the institution).
    Adds "Pending setup" section for institution admins to configure group/unit on newly assigned devices.
    Removes "Add device" from institution admin view — devices enter the system through physical provisioning only.
2026-06-15 Device assignment fixes
2026-06-15 More useful features
2026-06-15 Deleting institutions causes a cascade delete
2026-06-15 Security hardening: tenant isolation, TLS, provisioning tokens, schema fixes
    Fixes from a full adversarial code review across frontend, backend, firmware, and DB.
    Auth & tenant isolation
    - verifySession() now fails closed — no silent role default (C1)
    - Public signup disabled in Supabase config (C1)
    - New ownership.ts guard applied to all mutating actions: members, staff,
    devices, academic, enrollment, users, promotion (C2/C3/H4/H5/H6/M6)
2026-06-15 Fixed CA certificacte problems
2026-06-16 Updated Documentation
2026-06-16 Fixed /overview routing to /attendance
2026-06-16 Added attendance filtering by member
2026-06-18 Update attendance-view.tsx
    Fixed 'absent' records changing to 'present' when filtered for a single member
2026-06-21 Phase 1: shop type + cashier role (platform foundation)
    Adds the DB and frontend plumbing for GENERAL LOCKS without creating any
    retail tables. Migration 20260620120000 widens the two existing CHECK
    constraints — institutions.type += 'shop', profiles.role += 'cashier' —
    using the established drop+re-add pattern; not yet applied to cloud.
    Frontend: InstitutionConfig.type and UserRole both updated; sidebar,
    mobile nav and header handle shop type (no Members, no Promotion, Academic
2026-06-21 Fixed institution device info leaking in accounts page
2026-06-21 Phase 3 (Added products/services catalog)
2026-06-21 Phase 5 (Sales recording)
2026-06-23 Update sale-dialog.tsx
    -Changed sales dropdowns to search and dropdowns
2026-06-24 Phase 6 (Loyalty rewards)
    Reward rule config + manual issuance for shop tenants.
    - /rewards page (super_admin/admin only; cashier excluded)
    - Rules tab: CRUD over the rich reward model — condition
    (service/product/visit count or amount spent, optional catalog
    scoping, lifetime/rolling/since-last-issuance window, repeatable)
    + payload (free service/product, discount, or custom)
2026-06-27 Shop architecture: currency, offerings, deactivation, loyalty toggles
    - Per-institution ISO-4217 currency (institutions.currency); all money
    formatting routed through formatMoney(); reports + CSV exports honour
    tenant currency, takings export honours tenant timezone
    - Module-level offerings toggles (sell_products / sell_services) gating
    catalog page/tabs, sales picker, and nav
    - Institution lifecycle status (active/suspended/deactivated): enforced
2026-06-27 Fixed attendance and staff pages showing up for cashiers
2026-06-27 Fix logo fallback, nav loader, shop labels, visit→sale flow, 404 redirect, and sales/rewards pagination
